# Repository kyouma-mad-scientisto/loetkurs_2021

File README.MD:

Dieses kleine Badge habe ich 2021 für einen Lötkurs an meiner Hochschule entworfen. Damit sollten die Teilnehmer SMD löten üben. Am Ende konnten sie ihr Werk mit nach Hause nehmen und nach belieben programmieren.
Anlässlich des Girl's Days habe ich in einer späteren Iteration noch einen CH340 ergänzt, damit der Controller ohne extra Hardware programmiert werden kann, es wird nur noch ein Mini-USB Kabel benötigt.

FuldAIno vorn<br />

FuldAIno hinten<br />

FuldAIno im Betrieb<br />

IM WEITEREN FOLGT DIE ORIGINALE README.md
###########################################################################################################################################################################################################################

FuldAIno - eine 8x8 LED Matrix gesteuert von einem Atmega328p

Soll FuldAIno nach dem bestücken der Leiterplatte Arduino kompatibel sein, muss zunächst mit einem AVR ISP Flasher, über den 6 pol. ISP Anschluss, der Bootloader auf den Atmega328p gebrannt werden.
Den passenden Bootloader bzw. die passende Bibliothek für das Projekt findet ihr unter: https://github.com/oshlab/Breadboard-Arduino
Bitte zunächst den Anweisungen auf obiger Webseite folgen.
Pinbelegung auf der Platine (Draufsicht).

```
	1  2
       -------
MISO   | o o |  Vcc (5V)
SCK   [  o o |  MOSI
RESET  | o o |  GND
       -------
```

Danach wird ein einfacher USB-Serial Adapter benötigt. Diese findet man sehr günstig bei eBay, aliexpress und co. z.B. unter folgendem Namen: USB zu Serial TTL FT232RL
Hierbei sollte auch auf das Vorhandensein des DTR Pins geachtet werden, dieser wird benötigt, damit die Arduino IDE den Controller zum flashen zurücksetzen kann.
Außerdem empfehle ich gleich einen Adapter zu kaufen, welcher auch für 3,3V Logik geeignet ist, so sind auch zukünftige Projekte mit 3,3V Bauteilen, wie z.B. dem Arduino Pro Mini oder dem ESP32 kein Problem.
Pinbelegung auf der Platine (Draufsicht).

```
        ---
GND     |o|
Vcc(5V) |o|
Rx      |o|
Tx      |o|
DTR     |o|
        ---
```

Den seriellen Adapter entsprechend der obigen Belegung mit dem FuldAIno verbinden (Achtung! TX muss jeweils auf RX), nochmal alles kontrollieren, doppelt hält besser  ;).
Nun den Adapter mit dem PC verbinden, das FuldAIno Demoprojekt öffnen, den korrekten Port und das korrekte Board (Breadboard Arduino (OSHLAB.com) -> Atmega328p (8MHz internal)) auswählen und dann, oben links,
auf den blauen Pfeil klicken (hochladen) und warten, bis der Vorgang abgeschlossen ist.

Hinweise zum Demoprojekt:

Für die regelmäßge Aktualisierung der Anzeige wird der Timer1 des Atmegas beansprucht. Dieser kann also nicht für andere Dinge verwendet werden. Ihr könnt aber die ISR, welche in "ScanLines.ino" ab Zeile 13
beginnt für KURZE Funktionen nutzen, welche regelmäßig ausgeführt werden sollen.
Die Funktion "scanLines()" muss IMMER in der Timer1 ISR ausgeführt werden, sonst findet keine Aktualisierung der Anzeige mehr statt.
Die Datei "ScanLines.ino" am besten garnicht verändern, außer ihr möchtet die LEDs direkt ansteuern, ohne den Framebuffer.

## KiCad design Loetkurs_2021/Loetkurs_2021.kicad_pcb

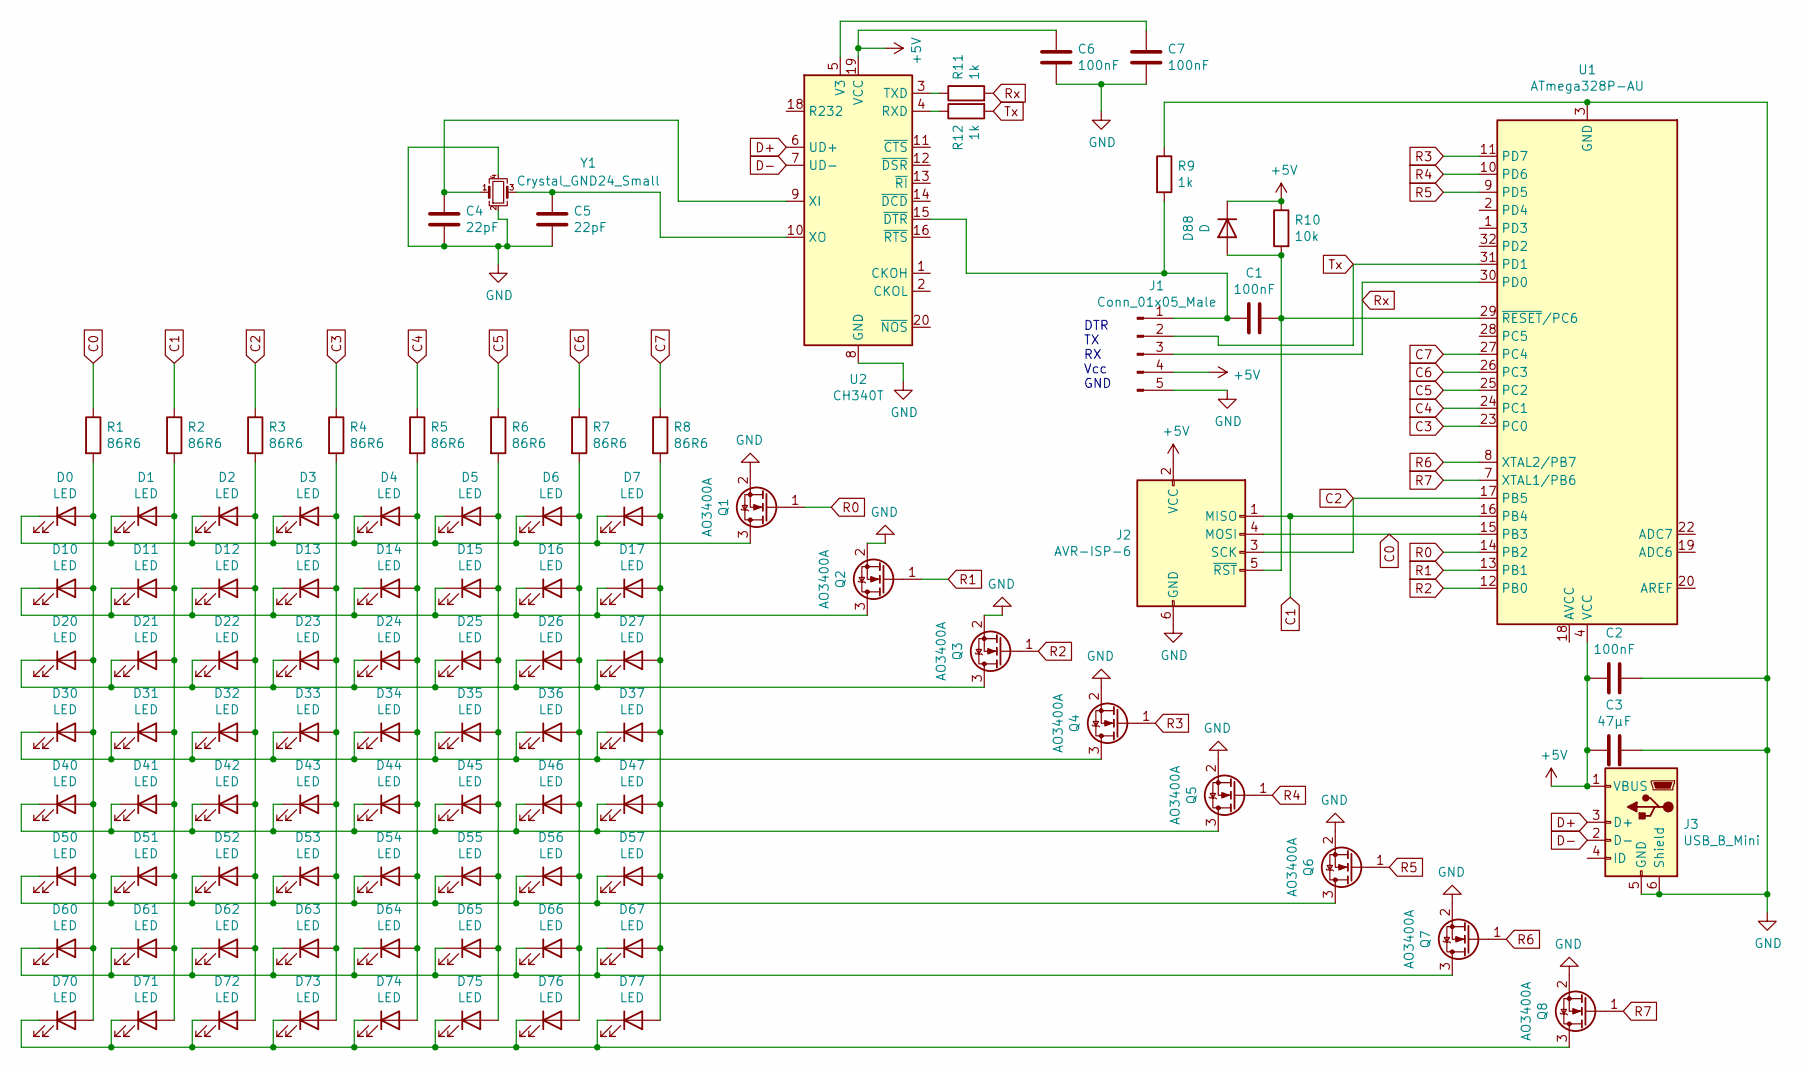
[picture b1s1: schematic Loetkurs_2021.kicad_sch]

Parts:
C1, C2, C6, C7: 100nF; C_0402_1005Metric_Pad0.74x0.62mm_HandSolder
C3: 47µF; C_0805_2012Metric_Pad1.18x1.45mm_HandSolder
C4, C5: 22pF; C_0402_1005Metric_Pad0.74x0.62mm_HandSolder
D0, D1, D2, D3, D4, D5, D6, D7, D10, D11, D12, D13, D14, D15, D16, D17, D20, D21, D22, D23, D24, D25, D26, D27, D30, D31, D32, D33, D34, D35, D36, D37, D40, D41, D42, D43, D44, D45, D46, D47, D50, D51, D52, D53, D54, D55, D56, D57, D60, D61, D62, D63, D64, D65, D66, D67, D70, D71, D72, D73, D74, D75, D76, D77: LED; LED_0603_1608Metric_Pad1.05x0.95mm_HandSolder
D88: D; D_0805_2012Metric_Pad1.15x1.40mm_HandSolder
J1: Conn_01x05_Male; Arduino_Pro_Mini_Serial_Connector
J2: AVR-ISP-6; AVR_ISP_6Pin_Connector
J3: USB_B_Mini; USB_Mini-B_Wuerth_65100516121_Horizontal
Q1, Q2, Q3, Q4, Q5, Q6, Q7, Q8: AO3400A; SOT-23
R1, R2, R3, R4, R5, R6, R7, R8: 86R6; R_0402_1005Metric_Pad0.72x0.64mm_HandSolder
R9, R11, R12: 1k; R_0402_1005Metric_Pad0.72x0.64mm_HandSolder
R10: 10k; R_0402_1005Metric_Pad0.72x0.64mm_HandSolder
U1: ATmega328P-AU; TQFP-32_7x7mm_P0.8mm
U2: CH340T; SSOP-20_5.3x7.2mm_P0.65mm
Y1: Crystal_GND24_Small; Crystal_SMD_Abracon_ABM8G-4Pin_3.2x2.5mm

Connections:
C0: J2.4 (MOSI), R1.1, U1.15 (PB3)
C1: J2.1 (MISO), R2.1, U1.16 (PB4)
C2: J2.3 (SCK), R3.1, U1.17 (PB5)
C3: R4.1, U1.23 (PC0)
C4: R5.1, U1.24 (PC1)
C5: R6.1, U1.25 (PC2)
C6: R7.1, U1.26 (PC3)
C7: R8.1, U1.27 (PC4)
D+: J3.3 (D+), U2.6 (UD+)
D-: J3.2 (D-), U2.7 (UD-)
GND: C2.1, C3.1, C4.2, C5.2, C6.2, C7.2, J1.5, J2.6 (GND), J3.5 (GND), J3.6 (Shield), Q1.2 (S), Q2.2 (S), Q3.2 (S), Q4.2 (S), Q5.2 (S), Q6.2 (S), Q7.2 (S), Q8.2 (S), R9.1, U1.3 (GND), U1.5 (GND), U1.21 (GND), U2.8 (GND), Y1.2, Y1.4
unnamed: C1.1, J1.1, R9.2, U2.15 (~DTR)
unnamed: C1.2, D88.2 (A), J2.5 (~RST), R10.2, U1.29 (~RESET/PC6)
unnamed: C4.1, U2.9 (XI), Y1.1
unnamed: C5.1, U2.10 (XO), Y1.3
unnamed: C7.1, U2.5 (V3)
unnamed: D0.1 (K), D1.1 (K), D2.1 (K), D3.1 (K), D4.1 (K), D5.1 (K), D6.1 (K), D7.1 (K), Q1.3 (D)
unnamed: D0.2 (A), D10.2 (A), D20.2 (A), D30.2 (A), D40.2 (A), D50.2 (A), D60.2 (A), D70.2 (A), R1.2
unnamed: D1.2 (A), D11.2 (A), D21.2 (A), D31.2 (A), D41.2 (A), D51.2 (A), D61.2 (A), D71.2 (A), R2.2
unnamed: D10.1 (K), D11.1 (K), D12.1 (K), D13.1 (K), D14.1 (K), D15.1 (K), D16.1 (K), D17.1 (K), Q2.3 (D)
unnamed: D2.2 (A), D12.2 (A), D22.2 (A), D32.2 (A), D42.2 (A), D52.2 (A), D62.2 (A), D72.2 (A), R3.2
unnamed: D3.2 (A), D13.2 (A), D23.2 (A), D33.2 (A), D43.2 (A), D53.2 (A), D63.2 (A), D73.2 (A), R4.2
unnamed: D4.2 (A), D14.2 (A), D24.2 (A), D34.2 (A), D44.2 (A), D54.2 (A), D64.2 (A), D74.2 (A), R5.2
unnamed: D5.2 (A), D15.2 (A), D25.2 (A), D35.2 (A), D45.2 (A), D55.2 (A), D65.2 (A), D75.2 (A), R6.2
unnamed: D6.2 (A), D16.2 (A), D26.2 (A), D36.2 (A), D46.2 (A), D56.2 (A), D66.2 (A), D76.2 (A), R7.2
unnamed: D7.2 (A), D17.2 (A), D27.2 (A), D37.2 (A), D47.2 (A), D57.2 (A), D67.2 (A), D77.2 (A), R8.2
unnamed: D20.1 (K), D21.1 (K), D22.1 (K), D23.1 (K), D24.1 (K), D25.1 (K), D26.1 (K), D27.1 (K), Q3.3 (D)
unnamed: D30.1 (K), D31.1 (K), D32.1 (K), D33.1 (K), D34.1 (K), D35.1 (K), D36.1 (K), D37.1 (K), Q4.3 (D)
unnamed: D40.1 (K), D41.1 (K), D42.1 (K), D43.1 (K), D44.1 (K), D45.1 (K), D46.1 (K), D47.1 (K), Q5.3 (D)
unnamed: D50.1 (K), D51.1 (K), D52.1 (K), D53.1 (K), D54.1 (K), D55.1 (K), D56.1 (K), D57.1 (K), Q6.3 (D)
unnamed: D60.1 (K), D61.1 (K), D62.1 (K), D63.1 (K), D64.1 (K), D65.1 (K), D66.1 (K), D67.1 (K), Q7.3 (D)
unnamed: D70.1 (K), D71.1 (K), D72.1 (K), D73.1 (K), D74.1 (K), D75.1 (K), D76.1 (K), D77.1 (K), Q8.3 (D)
unnamed: R11.1, U2.3 (TXD)
unnamed: R12.1, U2.4 (RXD)
R0: Q1.1 (G), U1.14 (PB2)
R1: Q2.1 (G), U1.13 (PB1)
R2: Q3.1 (G), U1.12 (PB0)
R3: Q4.1 (G), U1.11 (PD7)
R4: Q5.1 (G), U1.10 (PD6)
R5: Q6.1 (G), U1.9 (PD5)
R6: Q7.1 (G), U1.8 (XTAL2/PB7)
R7: Q8.1 (G), U1.7 (XTAL1/PB6)
Rx: J1.3, R11.2, U1.30 (PD0)
Tx: J1.2, R12.2, U1.31 (PD1)

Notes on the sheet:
DTR TX RX Vcc GND

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
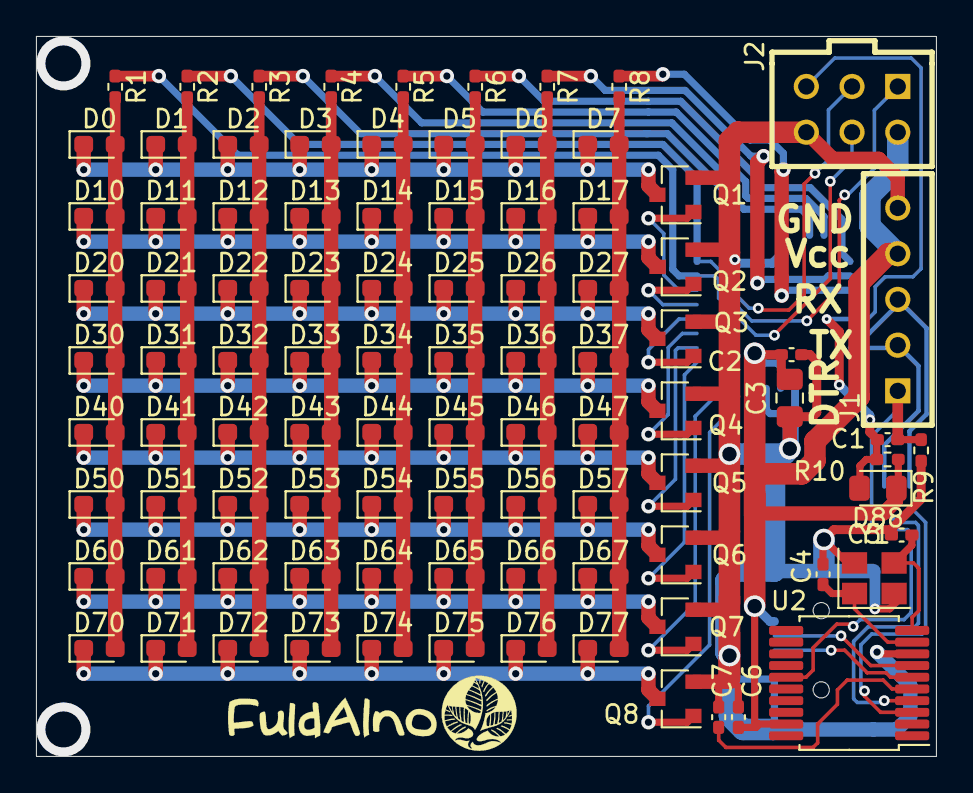
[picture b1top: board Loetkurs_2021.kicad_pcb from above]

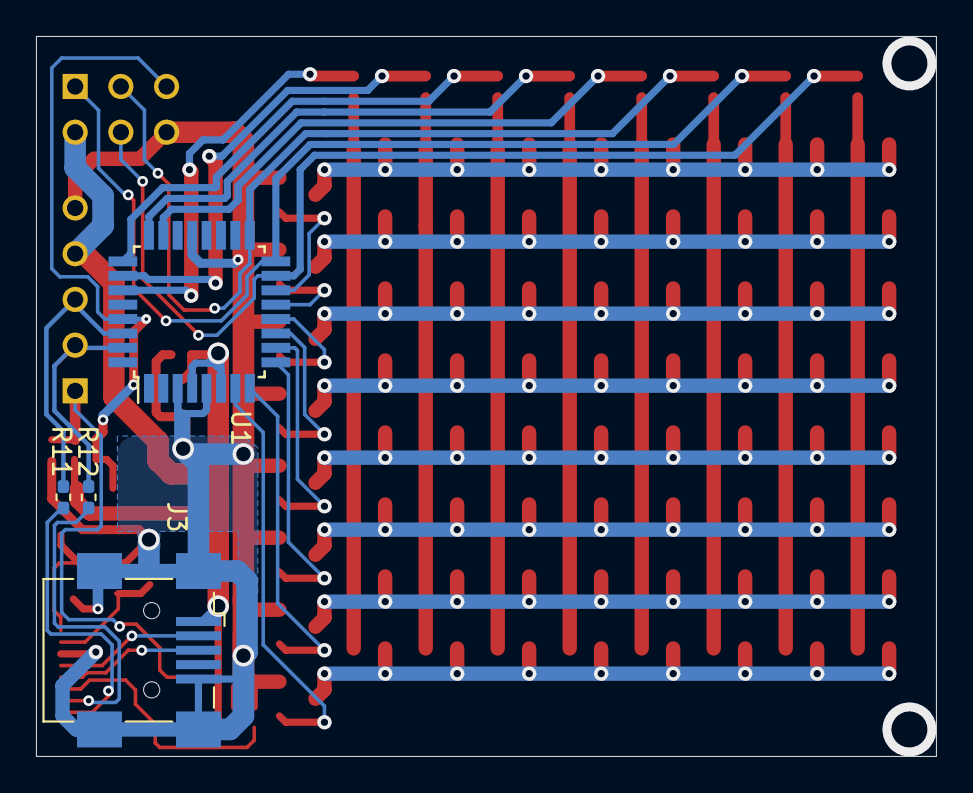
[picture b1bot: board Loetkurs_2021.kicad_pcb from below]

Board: 2 copper layers, 50.0 x 40.0 mm, 98 parts (4 on the bottom side), 45 nets.

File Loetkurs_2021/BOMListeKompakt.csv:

Ref,Value,Footprint,,Ref,Value,Footprint
C1+C2,100nF,0402,,C1+C2,100nF,0402
C3,47µF,0805,,C3,47µF,0805
D0-D77,LED,0603,,D0-D77,LED,0603
D88,Diode,0805,,D88,Diode,0805
J1,,1x5 Stiftleiste,,J1,,1x5 Stiftleiste
J2,,2x3 Stiftleiste,,J2,,2x3 Stiftleiste
J3,,USB_B_Mini,,J3,,USB_B_Mini
Q1-Q8,AO3400A,SOT-23,,Q1-Q8,AO3400A,SOT-23
R1-R8,86R6,0402,,R1-R8,86R6,0402
R9,1k,0402,,R9,1k,0402
R10,10k,0402,,R10,10k,0402
U1,ATmega328P-AU,TQFP,,U1,ATmega328P-AU,TQFP
,,,,,,
Ref,Value,Footprint,,Ref,Value,Footprint
C1+C2,100nF,0402,,C1+C2,100nF,0402
C3,47µF,0805,,C3,47µF,0805
D0-D77,LED,0603,,D0-D77,LED,0603
D88,Diode,0805,,D88,Diode,0805
J1,,1x5 Stiftleiste,,J1,,1x5 Stiftleiste
J2,,2x3 Stiftleiste,,J2,,2x3 Stiftleiste
J3,,USB_B_Mini,,J3,,USB_B_Mini
Q1-Q8,AO3400A,SOT-23,,Q1-Q8,AO3400A,SOT-23
R1-R8,86R6,0402,,R1-R8,86R6,0402
R9,1k,0402,,R9,1k,0402
R10,10k,0402,,R10,10k,0402
U1,ATmega328P-AU,TQFP,,U1,ATmega328P-AU,TQFP
,,,,,,
Ref,Value,Footprint,,Ref,Value,Footprint
C1+C2,100nF,0402,,C1+C2,100nF,0402
C3,47µF,0805,,C3,47µF,0805
D0-D77,LED,0603,,D0-D77,LED,0603
D88,Diode,0805,,D88,Diode,0805
J1,,1x5 Stiftleiste,,J1,,1x5 Stiftleiste
J2,,2x3 Stiftleiste,,J2,,2x3 Stiftleiste
J3,,USB_B_Mini,,J3,,USB_B_Mini
Q1-Q8,AO3400A,SOT-23,,Q1-Q8,AO3400A,SOT-23
R1-R8,86R6,0402,,R1-R8,86R6,0402
R9,1k,0402,,R9,1k,0402
R10,10k,0402,,R10,10k,0402
U1,ATmega328P-AU,TQFP,,U1,ATmega328P-AU,TQFP
,,,,,,
Ref,Value,Footprint,,Ref,Value,Footprint
C1+C2,100nF,0402,,C1+C2,100nF,0402
C3,47µF,0805,,C3,47µF,0805
D0-D77,LED,0603,,D0-D77,LED,0603
D88,Diode,0805,,D88,Diode,0805
J1,,1x5 Stiftleiste,,J1,,1x5 Stiftleiste
J2,,2x3 Stiftleiste,,J2,,2x3 Stiftleiste
J3,,USB_B_Mini,,J3,,USB_B_Mini
Q1-Q8,AO3400A,SOT-23,,Q1-Q8,AO3400A,SOT-23
R1-R8,86R6,0402,,R1-R8,86R6,0402
R9,1k,0402,,R9,1k,0402
R10,10k,0402,,R10,10k,0402
U1,ATmega328P-AU,TQFP,,U1,ATmega328P-AU,TQFP

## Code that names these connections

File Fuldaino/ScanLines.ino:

/*
 * Displayaktualisierung
 * alle 8ms = 125Hz
 */

#define TIMER_INTERVAL_MS  1  //* 8 = 8ms
const uint16_t TIMER1_COUNT = TIMER_INTERVAL_MS / ((float)1 / 8000 * 256) / 8;

const uint8_t FRAMEBUFFER_SIZE = 8;
volatile static uint8_t framebuffer[FRAMEBUFFER_SIZE];
volatile static bool inverted = false;

//Timer1 ISR
ISR(TIMER1_COMPA_vect)
{
  scanLines();
  //hier koennten noch weitere KURZE Befehle ausgefuehrt werden
}
//wechselt regelmaessig die Zeile
void scanLines() {
  static uint8_t line = 0;

  if(line < 7) {
    line++;
  } else {
    line = 0;
  }

  uint8_t lineOutput = (128 >> line);
  uint8_t columns = framebuffer[line];

  setOutputs(lineOutput, columns);
}
void setOutputs(uint8_t lineOutput, uint8_t columns)
{
  //PinBelegung FuldAIno
  //zuerst Zeilentreiber deaktivieren um Flackern/Artefakte zu vermeiden
  PORTB &= 0b00111000;
  PORTD &= 0b00011111;
  //nun den Spaltentreiber loeschen
  PORTB &= 0b11000111;
  PORTC &= 0b11100000;
  //wenn invertiert dann
  if(inverted)
  {
    //nun die neue Zeile invertiert in den Spaltentreiber laden 
    PORTB |= (0b00111000 & ((~columns & 0b00000111) << 3));
    PORTC |= (0b00011111 & ((~columns & 0b11111000) >> 3));    
  } else {
    //nun die neue Zeile in den Spaltentreiber laden 
    PORTB |= (0b00111000 & ((columns & 0b00000111) << 3));
    PORTC |= (0b00011111 & ((columns & 0b11111000) >> 3));
  }
  //zuletzt den Zeilentreiber wieder einschalten
  PORTB |= (0b11000111 & (((lineOutput & 0b11100000) >> 5) | ((lineOutput & 0b00000011) << 6)));
  PORTD |= (0b11100000 & ((lineOutput & 0b00011100) << 3));

}
//den kompletten Framebuffer ueberschreiben
void changeFramebuffer(char* newBuffer)
{
  for(uint8_t i=0; i<8; i++)
  {
    framebuffer[i] = newBuffer[i];
  }
}
//eine Zeile des Framebuffers aendern
void changeFramebufferLine(char line, uint8_t lineNumber)
{
  framebuffer[lineNumber] = line;  
}
//setzt ein Pixel
void setPixel(uint8_t x, uint8_t y)
{
  if((x < 8) || (y < 8)) {
    framebuffer[y] |= (0x01 << (x));
  }
}
//loescht ein Pixel
void clearPixel(uint8_t x, uint8_t y)
{
  if((x < 8) || (y < 8)) {
    framebuffer[y] &= ~(0x01 << (x));
  }
}
//Zustand eines Pixels beziehen
bool getPixel(uint8_t x, uint8_t y) {
  bool pixelState = false;

  if((x < 8) || (y < 8)) {
    pixelState = (framebuffer[y] >> (x)) & 0x01;
  }
  return pixelState;
}
//komplettes Display loeschen
void clearDisplay()
{
  for(uint8_t i=0; i<FRAMEBUFFER_SIZE; i++)
  {
    framebuffer[i] = 0;
  }
}
//invertiert die Darstellung
void invertDisplay(bool invert)
{
  inverted = invert;
}
//setup
void initScanning() {
  DDRB = 0xFF;
  DDRC = 0b00011111;
  DDRD = 0b11100000;
//alle Ports loeschen
  PORTB = 0;
  PORTC = 0b11100000;
  PORTD = 0b00011111;
//framebuffer loeschen
  for(uint8_t i = 0; i < FRAMEBUFFER_SIZE; i++){
    framebuffer[i] = 0;
  }
//Timer1 konfigurieren
  noInterrupts();
  TCCR1A = 0; //set TCCRXA register to 0
  TCCR1B = 0; //set TCCRXB register to 0
  TCNT1 = 0; //reset counter value
    
  OCR1A = TIMER1_COUNT; //set compare match register of timer1
    
  TCCR1B |= (1 << WGM12); //enable timer1 CTC mode
  //1:1024
  TCCR1B |= (1 << CS12); //set prescaler bits
  //Timer einschalten
  TIMSK1 |= (1 << OCIE1A); //enable timer1 compare interrupt  
  interrupts();
}

/*
Pinmapping:

Panel  - Controller

C0  - PB3
C1  - PB4
C2  - PB5
C3  - PC0
C4  - PC1
C5  - PC2
C6  - PC3
C7  - PC4

R0  - PB2
R1  - PB1
R2  - PB0
R3  - PD7
R4  - PD6
R5  - PD5
R6  - PB7
R7  - PB6
*/

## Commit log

2021-09-11 bezeichnungen am Panel geaendert
2021-09-12 kleine Aenderungen am Schaltplan (Werte)
2021-09-12 Benennung LEDs geändert
2021-09-12 doppelte Bezeichnungen gefixt
2021-09-12 Projekteinstellungen aktualisiert
2021-09-30 BOM ergaenzt
2021-09-30 Kompakte BOM-Liste hinzugefügt
2021-10-01 erste Demo
2021-10-02 Testprogramm fertig
2021-10-02 Kommentare added
2021-10-04 Problem mit Bitoperationen gefixt
2021-10-05 Setup Routine optimiert
2021-10-08 README ergaenzt
2021-10-11 BOM-Liste aktualisiert
2021-10-11 Formatierung Read me
2021-11-26 ch340 hinzugefuegt
2021-11-27 fast fertig
2022-10-11 FuldAIno mit CH340 fertiggestellt
2022-10-16 Footprint einer Diode korrigiert
2023-11-21 Display-Darstellung kann jetzt invertiert werden \nDisplay kann jetzt per Funktionsaufruf geloescht werden \nneue Demomuster hinzugefuegt
2024-03-19 files added
2024-08-22 added pictures and demo video
2024-08-22 added picture links
2024-08-26 added picture
